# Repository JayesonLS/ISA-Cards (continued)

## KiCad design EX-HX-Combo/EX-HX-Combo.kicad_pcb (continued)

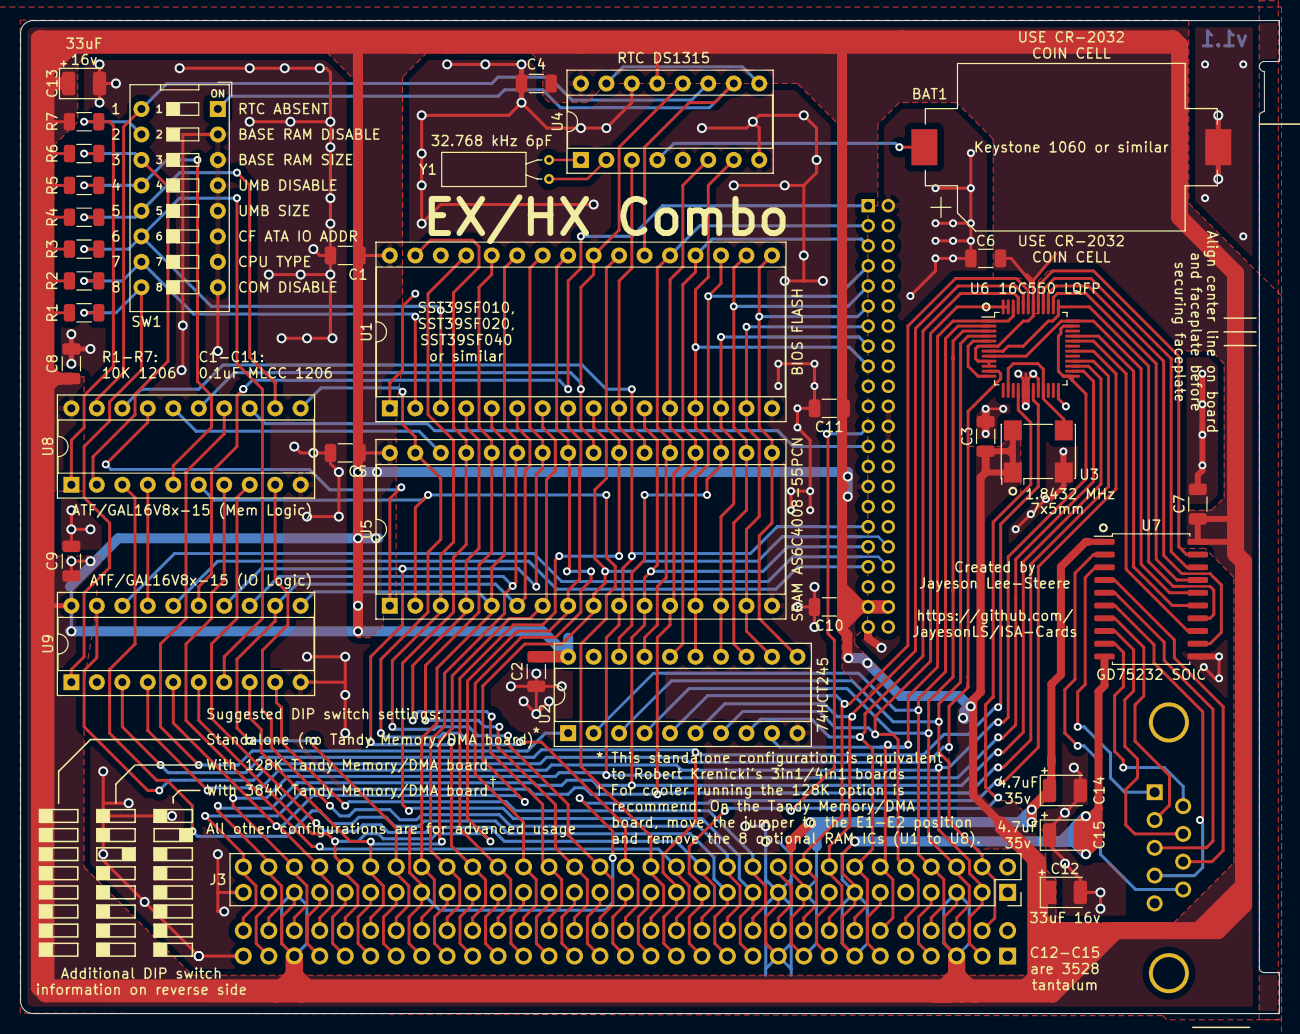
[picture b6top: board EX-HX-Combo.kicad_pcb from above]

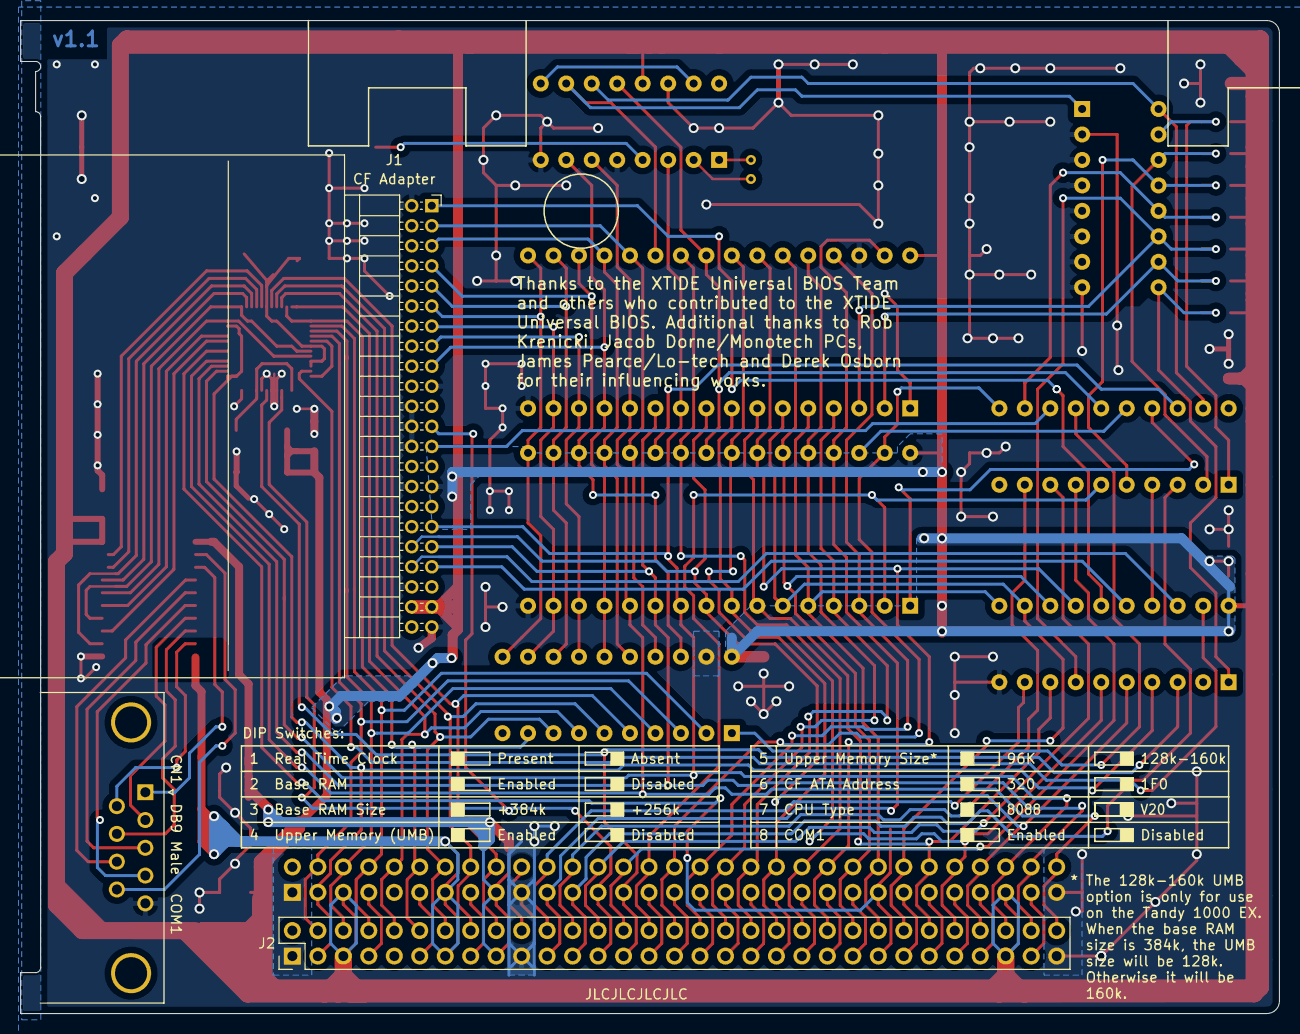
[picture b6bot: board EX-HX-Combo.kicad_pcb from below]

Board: 2 copper layers, 125.5 x 99.0 mm, 38 parts (2 on the bottom side), 107 nets.

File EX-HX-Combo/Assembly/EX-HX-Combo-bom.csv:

Comment,Designator,Footprint,LCSC
"CR2032","BAT1","Battery:BatteryHolder_Keystone_1060_1x2032",""
"0.1uF","C1,C2,C3,C4,C5,C6,C7,C8,C9,C10,C11","Capacitor_SMD:C_1206_3216Metric"," C24497"
"33uF 16v","C12,C13","Capacitor_Tantalum_SMD:CP_EIA-3528-15_AVX-H",""
"4.7uF 35v","C14,C15","Capacitor_Tantalum_SMD:CP_EIA-3528-15_AVX-H",""
"DB9 Male","CN1","w_conn_d-sub:DB_9M",""
"MountingHole_Pad","H1,H2,H3,H4","MountingHole:MountingHole_3.5mm_Pad",""
"AlignmentHole_Pad","H5,H6,H7","00Custom:AlignmentHole",""
"DB-9 Faceplate","H8","00Custom:DB9_Face",""
"IDE_CONNECTOR","J1","Connector_PinSocket_2.00mm:PinSocket_2x22_P2.00mm_Horizontal",""
"Bus_Tandy_Plus","J2","00Custom:TandyPlusSocket",""
"Bus_Tandy_Plus_Through","J3","00Custom:TandyPlusSocket",""
"10K","R1,R2,R3,R4,R5,R6,R7","Resistor_SMD:R_1206_3216Metric","C17902"
"SW_DIP_x10","SW1","Button_Switch_THT:SW_DIP_SPSTx10_Slide_9.78x27.58mm_W7.62mm_P2.54mm",""
"BIOS FLASH","U1","Package_DIP:DIP-32_W15.24mm_Socket","C146583"
"74HCT245","U2","Package_DIP:DIP-20_W7.62mm_Socket","C72118"
"1.8432 MHz","U3","Oscillator:Oscillator_SMD_SeikoEpson_SG8002CA-4Pin_7.0x5.0mm","C386895"
"DS1315","U4","Package_DIP:DIP-16_W7.62mm_Socket","C72115"
"AS6C4008-55PCN","U5","Package_DIP:DIP-32_W15.24mm_Socket","C146583"
"16C550","U6","Package_QFP:LQFP-48_7x7mm_P0.5mm","C181382"
"GD75232N","U7","Package_SO:SOIC-20W_7.5x12.8mm_P1.27mm","C1499602"
"GAL16V8","U8,U9","Package_DIP:DIP-20_W7.62mm_Socket","C72118"
"32.768 kHz","Y1","Crystal:Crystal_C38-LF_D3.0mm_L8.0mm_Horizontal","C182062"

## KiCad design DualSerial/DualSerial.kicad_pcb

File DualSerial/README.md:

Dual Serial
============

*** IN PROGRESS ***

A simple ISA card adding two serial (COM) ports to a vintage PC. 
Created with early Tandy 1000's in mind which have no COM ports from the factory.

Configuration
-------------

Before installing, configure the port selection jumpers to COM ports not yet present 
in the system. Details are located on the board by the port jumpers.

Configure the IRQ jumpers to an approriate selection. For no IRQ, remove the IRQ jumper.
Suggested IRQ settings are located on the board by the IRQ jumpers.

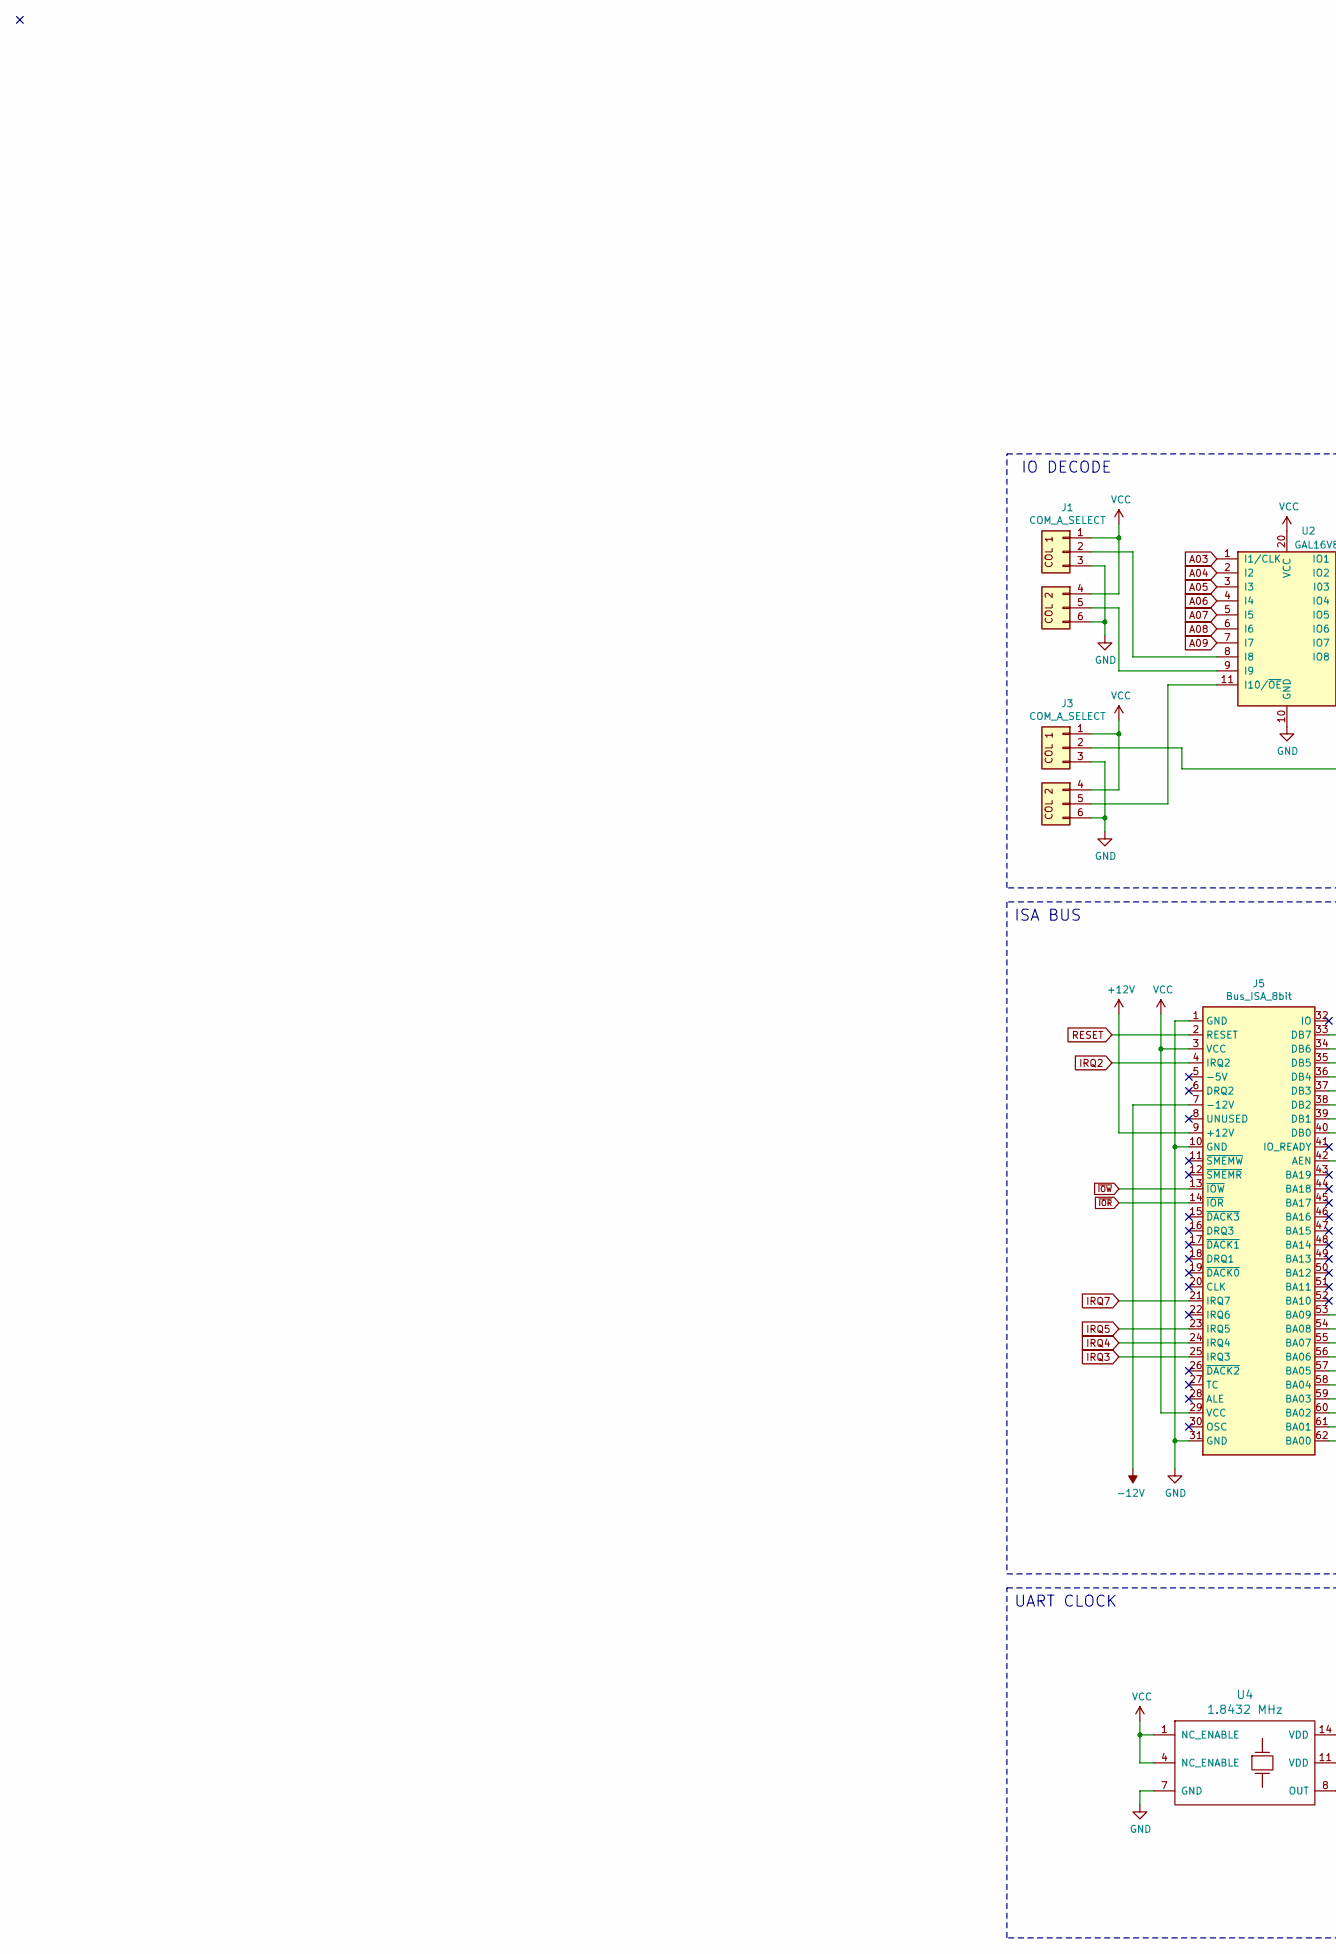
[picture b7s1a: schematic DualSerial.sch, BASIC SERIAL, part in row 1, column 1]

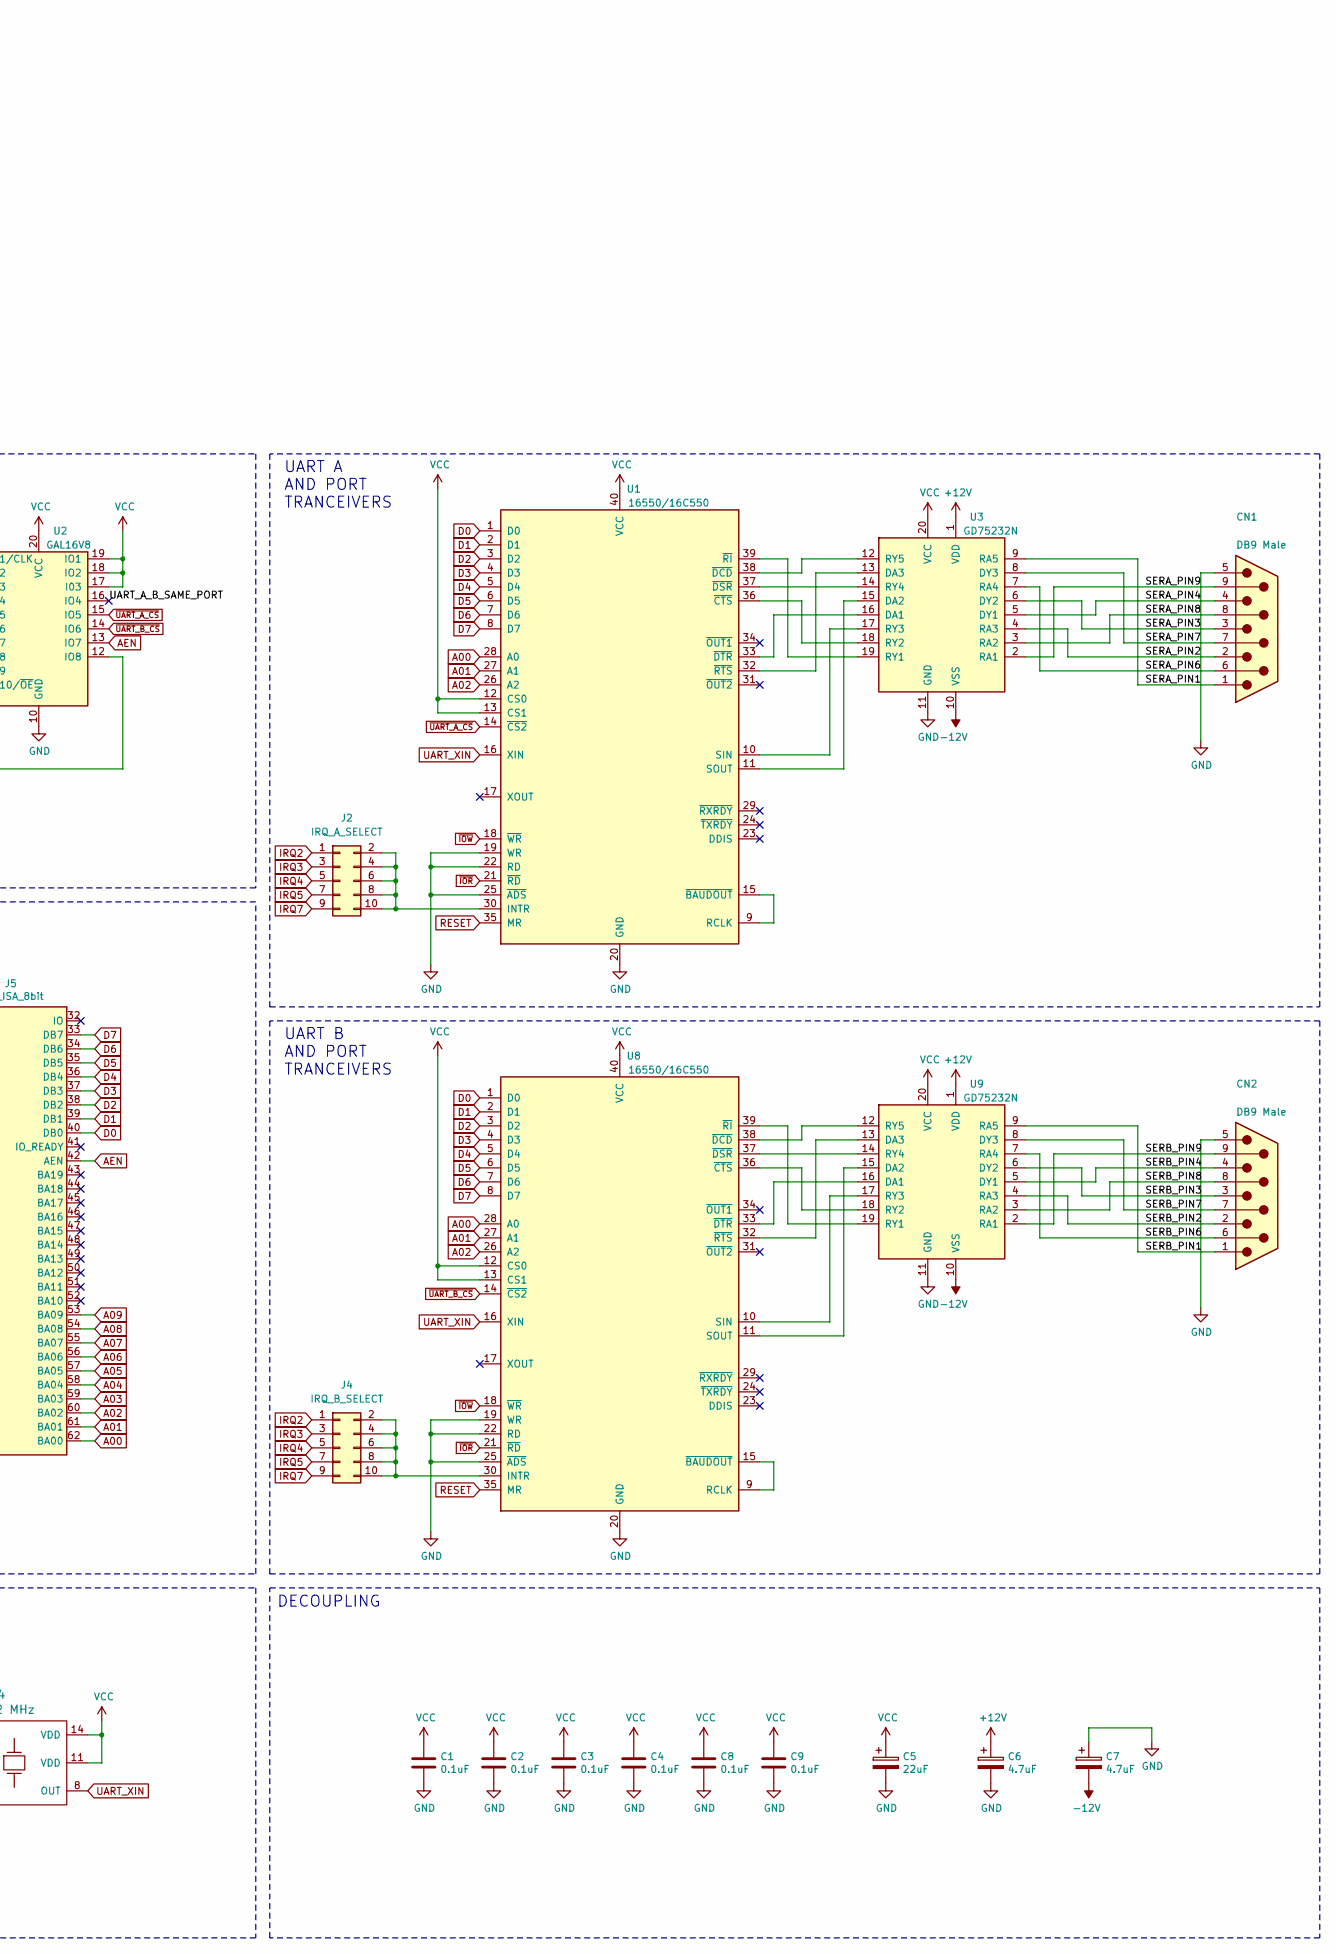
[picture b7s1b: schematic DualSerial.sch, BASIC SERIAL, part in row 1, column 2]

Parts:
C1, C2, C3, C4, C8, C9: 0.1uF; C_Disc_D5.1mm_W3.2mm_P5.00mm
C5: 22uF; CP_Radial_D7.5mm_P2.50mm
C6, C7: 4.7uF; CP_Radial_D7.5mm_P2.50mm
CN1, CN2: DB9 Male; DB_9M
J1, J3: COM_A_SELECT; PinHeader_3x02_P2.54mm_Vertical
J2: IRQ_A_SELECT; PinHeader_2x05_P2.54mm_Vertical
J4: IRQ_B_SELECT; PinHeader_2x05_P2.54mm_Vertical
J5: Bus_ISA_8bit; BUS_XT
U1, U8: 16550/16C550; DIP-40_W15.24mm_Socket
U2: GAL16V8; DIP-20_W7.62mm_Socket
U3, U9: GD75232N; DIP-20_W7.62mm_Socket
U4: 1.8432 MHz; Crystal_DIP8_DIP14

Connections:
+12V: C6.1, J5.9 (+12V), U3.1 (VDD), U9.1 (VDD)
-12V: C7.2, J5.7 (-12V), U3.10 (VSS), U9.10 (VSS)
/SERA_PIN1: CN1.1, U3.9 (RA5)
/SERA_PIN2: CN1.2, U3.4 (RA3)
/SERA_PIN3: CN1.3, U3.6 (DY2)
/SERA_PIN4: CN1.4, U3.5 (DY1)
/SERA_PIN6: CN1.6, U3.7 (RA4)
/SERA_PIN7: CN1.7, U3.8 (DY3)
/SERA_PIN8: CN1.8, U3.3 (RA2)
/SERA_PIN9: CN1.9, U3.2 (RA1)
/SERB_PIN1: CN2.1, U9.9 (RA5)
/SERB_PIN2: CN2.2, U9.4 (RA3)
/SERB_PIN3: CN2.3, U9.6 (DY2)
/SERB_PIN4: CN2.4, U9.5 (DY1)
/SERB_PIN6: CN2.6, U9.7 (RA4)
/SERB_PIN7: CN2.7, U9.8 (DY3)
/SERB_PIN8: CN2.8, U9.3 (RA2)
/SERB_PIN9: CN2.9, U9.2 (RA1)
/UART_A_B_SAME_PORT: U2.16 (IO4)
A00: J5.62 (BA00), U1.28 (A0), U8.28 (A0)
A01: J5.61 (BA01), U1.27 (A1), U8.27 (A1)
A02: J5.60 (BA02), U1.26 (A2), U8.26 (A2)
A03: J5.59 (BA03), U2.1 (I1/CLK)
A04: J5.58 (BA04), U2.2 (I2)
A05: J5.57 (BA05), U2.3 (I3)
A06: J5.56 (BA06), U2.4 (I4)
A07: J5.55 (BA07), U2.5 (I5)
A08: J5.54 (BA08), U2.6 (I6)
A09: J5.53 (BA09), U2.7 (I7)
AEN: J5.42 (AEN), U2.13 (IO7)
D0: J5.40 (DB0), U1.1 (D0), U8.1 (D0)
D1: J5.39 (DB1), U1.2 (D1), U8.2 (D1)
D2: J5.38 (DB2), U1.3 (D2), U8.3 (D2)
D3: J5.37 (DB3), U1.4 (D3), U8.4 (D3)
D4: J5.36 (DB4), U1.5 (D4), U8.5 (D4)
D5: J5.35 (DB5), U1.6 (D5), U8.6 (D5)
D6: J5.34 (DB6), U1.7 (D6), U8.7 (D6)
D7: J5.33 (DB7), U1.8 (D7), U8.8 (D7)
GND: C1.2, C2.2, C3.2, C4.2, C5.2, C6.2, C7.1, C8.2, C9.2, CN1.5, CN2.5, J1.3 (Pin_4), J1.6, J3.3 (Pin_4), J3.6, J5.1 (GND), J5.10 (GND), J5.31 (GND), U1.19 (WR), U1.20 (GND), U1.22 (RD), U1.25 (~ADS~), U2.10 (GND), U3.11 (GND), U4.7 (GND), U8.19 (WR), U8.20 (GND), U8.22 (RD), U8.25 (~ADS~), U9.11 (GND)
IRQ2: J2.1, J4.1, J5.4 (IRQ2)
IRQ3: J2.3, J4.3, J5.25 (IRQ3)
IRQ4: J2.5, J4.5, J5.24 (IRQ4)
IRQ5: J2.7, J4.7, J5.23 (IRQ5)
IRQ7: J2.9, J4.9, J5.21 (IRQ7)
unnamed: J1.2, U2.8 (I8)
unnamed: J1.5, U2.9 (I9)
unnamed: J2.2, J2.4, J2.6, J2.8, J2.10, U1.30 (INTR)
unnamed: J3.2, U2.12 (IO8)
unnamed: J3.5, U2.11 (I10/~OE~)
unnamed: J4.2, J4.4, J4.6, J4.8, J4.10, U8.30 (INTR)
unnamed: U1.10 (SIN), U3.17 (RY3)
unnamed: U1.11 (SOUT), U3.15 (DA2)
unnamed: U1.9 (RCLK), U1.15 (~BAUDOUT~)
unnamed: U1.32 (~RTS~), U3.13 (DA3)
unnamed: U1.33 (~DTR~), U3.16 (DA1)
unnamed: U1.36 (~CTS~), U3.18 (RY2)
unnamed: U1.37 (~DSR~), U3.14 (RY4)
unnamed: U1.38 (~DCD~), U3.12 (RY5)
unnamed: U1.39 (~RI~), U3.19 (RY1)
unnamed: U8.10 (SIN), U9.17 (RY3)
unnamed: U8.11 (SOUT), U9.15 (DA2)
unnamed: U8.9 (RCLK), U8.15 (~BAUDOUT~)
unnamed: U8.32 (~RTS~), U9.13 (DA3)
unnamed: U8.33 (~DTR~), U9.16 (DA1)
unnamed: U8.36 (~CTS~), U9.18 (RY2)
unnamed: U8.37 (~DSR~), U9.14 (RY4)
unnamed: U8.38 (~DCD~), U9.12 (RY5)
unnamed: U8.39 (~RI~), U9.19 (RY1)
RESET: J5.2 (RESET), U1.35 (MR), U8.35 (MR)
UART_XIN: U1.16 (XIN), U4.8 (OUT), U8.16 (XIN)
VCC: C1.1, C2.1, C3.1, C4.1, C5.1, C8.1, C9.1, J1.1, J1.4, J3.1, J3.4, J5.3 (VCC), J5.29 (VCC), U1.12 (CS0), U1.13 (CS1), U1.40 (VCC), U2.17 (I03), U2.18 (IO2), U2.19 (IO1), U2.20 (VCC), U3.20 (VCC), U4.1 (NC_ENABLE), U4.4 (NC_ENABLE), U4.11 (VDD), U4.14 (VDD), U8.12 (CS0), U8.13 (CS1), U8.40 (VCC), U9.20 (VCC)
~IOR: J5.14 (~IOR), U1.21 (~RD~), U8.21 (~RD~)
~IOW: J5.13 (~IOW), U1.18 (~WR~), U8.18 (~WR~)
~UART_A_CS: U1.14 (~CS2~), U2.15 (IO5)
~UART_B_CS: U2.14 (IO6), U8.14 (~CS2~)

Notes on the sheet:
ISA BUS
IO DECODE
UART A AND PORT TRANCEIVERS
UART CLOCK
DECOUPLING
UART B AND PORT TRANCEIVERS

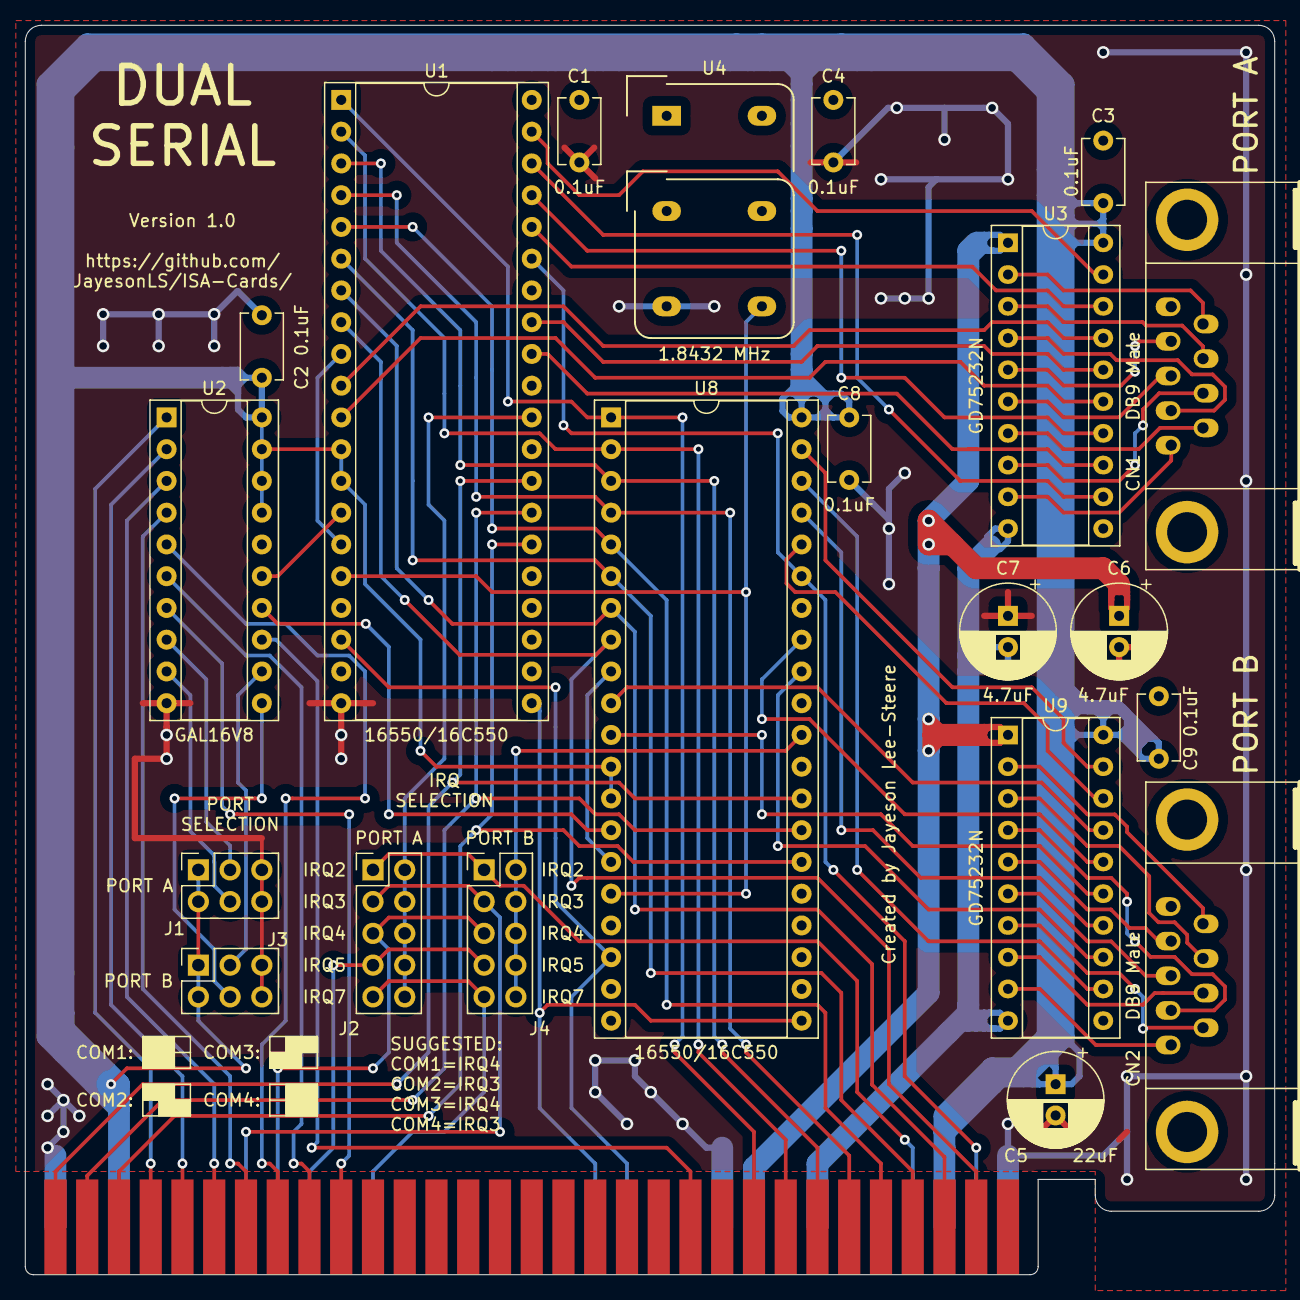
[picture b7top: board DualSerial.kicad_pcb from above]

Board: 2 copper layers, 99.9 x 99.9 mm, 22 parts (0 on the bottom side), 74 nets.

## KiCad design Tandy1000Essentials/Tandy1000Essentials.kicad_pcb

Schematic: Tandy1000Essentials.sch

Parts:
BAT1: CR2032; BatteryHolder_Keystone_103_1x20mm
C1, C2, C3, C4, C5, C6: 0.1uF; C_Disc_D6.0mm_W2.5mm_P5.00mm; Part options C84772,C263183; LCSC C84772
C7: 22uF; CP_Radial_D5.0mm_P2.50mm
H1, H2, H3, H4: MountingHole_Pad; MountingHole_3.5mm_Pad
J1: IDE_CONNECTOR; PinSocket_2x20_P2.54mm_Vertical
J2: CF Adapter Power; PinSocket_1x02_P2.54mm_Vertical
J3: Bus_ISA_8bit; BUS_XT
J4, J5: Addresses; PinHeader_2x03_P2.54mm_Vertical
U1: BIOS FLASH; DIP-32_W15.24mm_Socket
U2: 74HCT245; DIP-20_W7.62mm_Socket
U3: ATF/GAL22V10x-15; DIP-24_W7.62mm_Socket
U4: DS1315; DIP-16_W7.62mm_Socket
U5: AS6C4008-55PCN; DIP-32_W15.24mm_Socket
Y1: 32.768 KHz; Crystal_C38-LF_D3.0mm_L8.0mm_Horizontal

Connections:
/XTAL1: U4.1 (X1), Y1.1
/XTAL2: U4.2 (X2), Y1.2
A00: J3.62 (BA00), U1.12 (A0), U4.6 (D), U5.12 (A0)
A01: J1.35 (A0), J3.61 (BA01), U1.11 (A1), U5.11 (A1)
A02: J1.33 (A1), J3.60 (BA02), U1.10 (A2), U4.3 (~WE), U5.10 (A2)
A03: J1.36 (A2), J3.59 (BA03), U1.9 (A3), U5.9 (A3)
A04: J3.58 (BA04), U1.8 (A4), U3.1 (I1/CLK), U5.8 (A4)
A05: J3.57 (BA05), U1.7 (A5), U3.2 (I2), U5.7 (A5)
A06: J3.56 (BA06), U1.6 (A6), U3.3 (I3), U5.6 (A6)
A07: J3.55 (BA07), U1.5 (A7), U3.4 (I4), U5.5 (A7)
A08: J3.54 (BA08), U1.27 (A8), U3.5 (I5), U5.27 (A8)
A09: J3.53 (BA09), U1.26 (A9), U3.6 (I6), U5.26 (A9)
A10: J3.52 (BA10), U1.23 (A10), U5.23 (A10)
A11: J3.51 (BA11), U1.25 (A11), U5.25 (A11)
A12: J3.50 (BA12), U1.4 (A12), U5.4 (A12)
A13: J3.49 (BA13), U1.28 (A13), U5.28 (A13)
A14: J3.48 (BA14), U1.29 (A14), U5.3 (A14)
A15: J3.47 (BA15), U3.8 (I8), U5.31 (A15)
A16: J3.46 (BA16), U3.9 (I9), U5.2 (A16)
A17: J3.45 (BA17), U3.10 (I10), U5.30 (A17)
A18: J3.44 (BA18), U3.11 (I11), U5.1 (A18)
ATA_ADDR_JUMPER: J4.4, U1.3 (A15), U3.22 (IO2)
D0: J3.40 (DB0), U2.2 (A0)
D0_BUF: J1.17 (D0), U1.13 (D0), U2.18 (B0), U4.7 (Q), U5.13 (DQ0)
D1: J3.39 (DB1), U2.3 (A1)
D1_BUF: J1.15 (D1), U1.14 (D1), U2.17 (B1), U5.14 (DQ1)
D2: J3.38 (DB2), U2.4 (A2)
D2_BUF: J1.13 (D2), U1.15 (D2), U2.16 (B2), U5.15 (DQ2)
D3: J3.37 (DB3), U2.5 (A3)
D3_BUF: J1.11 (D3), U1.17 (D3), U2.15 (B3), U5.17 (DQ3)
D4: J3.36 (DB4), U2.6 (A4)
D4_BUF: J1.9 (D4), U1.18 (D4), U2.14 (B4), U5.18 (DQ4)
D5: J3.35 (DB5), U2.7 (A5)
D5_BUF: J1.7 (D5), U1.19 (D5), U2.13 (B5), U5.19 (DQ5)
D6: J3.34 (DB6), U2.8 (A6)
D6_BUF: J1.5 (D6), U1.20 (D6), U2.12 (B6), U5.20 (DQ6)
D7: J3.33 (DB7), U2.9 (A7)
D7_BUF: J1.3 (D7), U1.21 (D7), U2.11 (B7), U5.21 (DQ7)
unnamed: BAT1.1 (+), U4.4 (BAT1)
unnamed: U4.9 (ROM/~RAM), U4.15 (Vcc0)
RESET: J3.2 (RESET), U3.7 (I7)
ROM_ADDR_JUMPER: J4.3, U3.23 (IO1)
V20_JUMPER: J5.3, U1.2 (A16)
VCC: C1.1, C2.1, C3.1, C4.1, C5.1, C6.1, C7.1, J1.29 (~DACK), J1.38 (~CS3), J2.1, J3.3 (VCC), J3.29 (VCC), J4.1, J4.2, J5.1, U1.32 (VCC), U2.20 (VCC), U3.24 (VCC), U4.13 (~RST), U4.16 (Vcc1), U5.32 (VCC)
~CE~_BIOS: J5.4, U1.22 (CE)
~CE~_BIOS_DECODE: J5.2, U3.18 (IO6), U4.11 (~CEI)
~CE~_BIOS_THRU: J5.6, U4.10 (~CEO)
~CS1~_ATA: J1.37 (~CS1), U3.19 (IO5)
~IOR: J3.14 (~IOR), U3.21 (I03)
~IOR_OR_MEMR: U2.1 (A->B), U3.15 (IO9)
~IOR~_DELAYED: J1.25 (~IOR), U3.14 (IO10)
~IOW: J1.23 (~IOW), J3.13 (~IOW)
~MEMR: J3.12 (~SMEMR), U3.17 (IO7)
~MEMR~_DELAYED: U1.24 (OE), U3.16 (IO8), U4.12 (~OE), U5.24 (OE#)
~MEMW: J3.11 (~SMEMW), U1.31 (PGM), U5.29 (WE#)
~RESET: J1.1 (~RESET), U3.20 (IO4)

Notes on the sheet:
ISA BUS
DECOUPLING
DATA BUFFERING
DECODING
BIOS
CF ADAPTER
JUMPERS
REAL TIME CLOCK (OPTIONAL)
512K SRAM

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
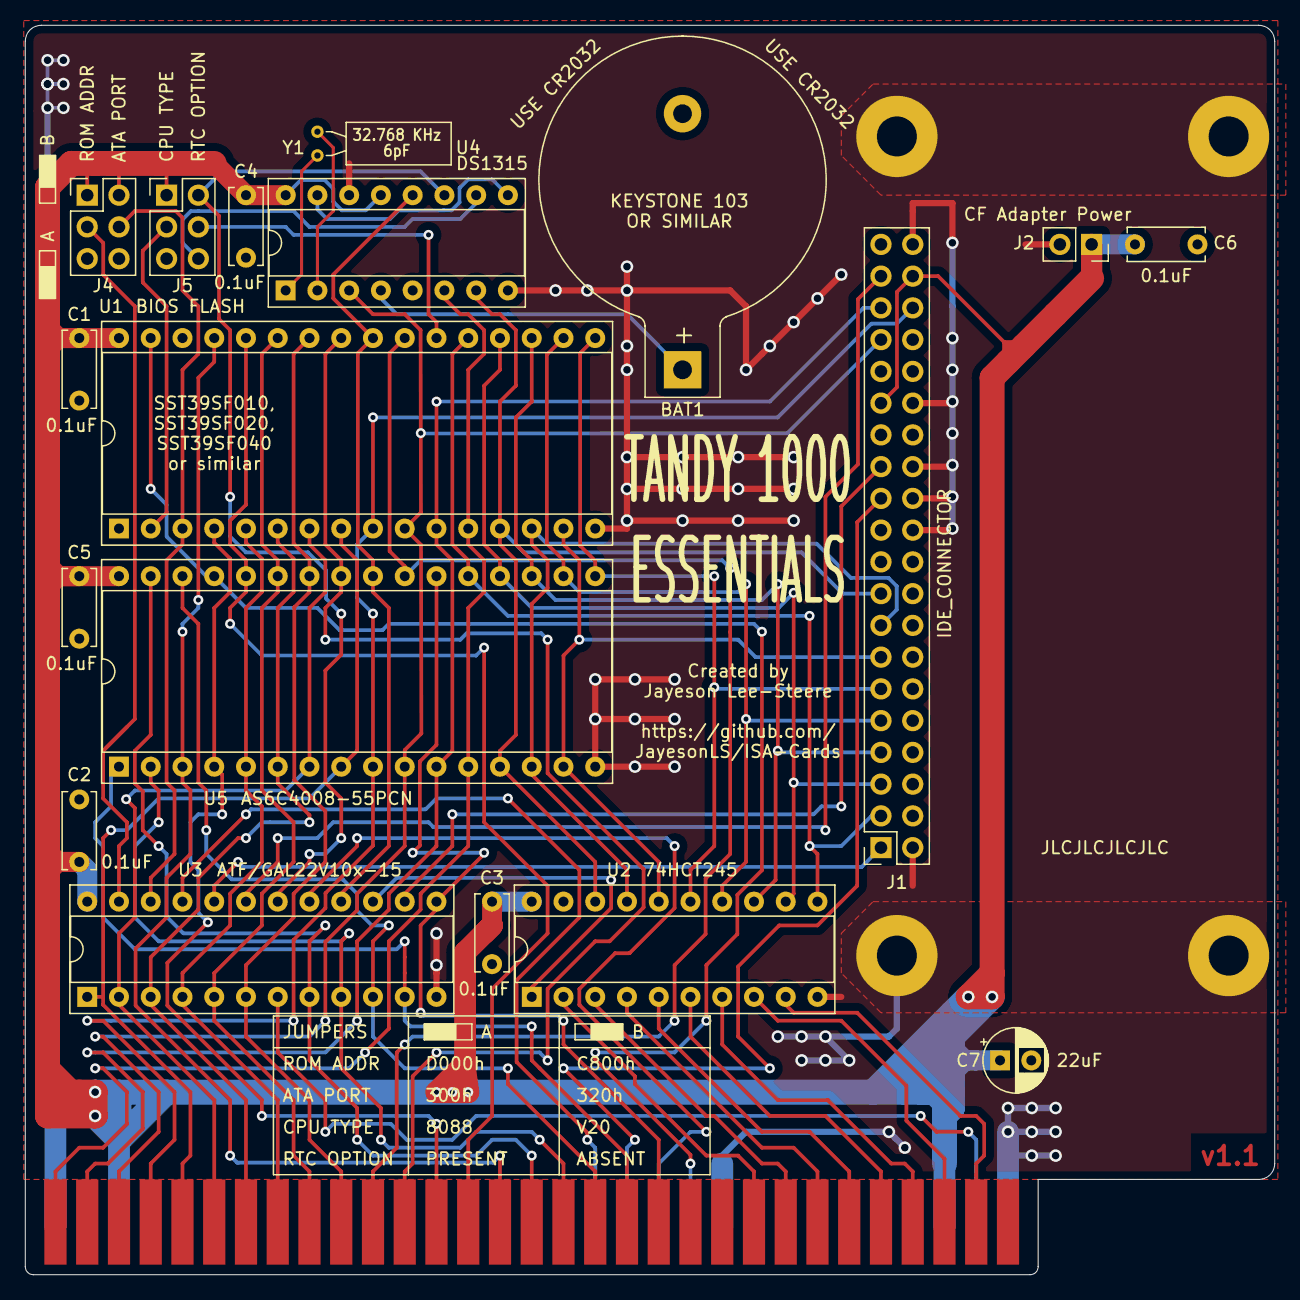
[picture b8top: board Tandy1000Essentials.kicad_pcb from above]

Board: 2 copper layers, 99.9 x 99.9 mm, 23 parts (0 on the bottom side), 58 nets.

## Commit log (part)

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2021-02-27 Add root LICENSE file.
2021-02-27 Add Libraries.
2021-02-27 Add Template board design.
2021-02-28 Add IDE/ATA connector to Template.
2021-02-28 Add global labels to the ISA bus connector,
2021-02-28 Add IC's to schematic and PCB.
2021-02-28 CF-Super-Lite: Label most IC pins and IDE connector.
2021-02-28 CF-Super-Lite: Added a bunch of premature layout.
2021-03-01 More premature layout work.
2021-03-02 Add power for CF adapter to Template and CF-Super-Lite.
2021-03-02 Finish remaining IDE signal directions based on the ATA spec rev 1. Correct IDE address assignments and route the new connections on the PCB.
2021-03-02 Removed /CS3 output from GAL as XT-IDE doesn't seem to use it. Wemoved A14 to GAL meaning BIOS now has a 32k range in memory rather than 16k. Used freed pins to implement RESET inversion.
2021-03-05 CF-Super-Lite: Final board tweaks before sending to production.
2021-03-05 CF-Super-Lite gerbers.
2021-03-13 CF-Super-Lite: Swap dip switch and resistor array for jumper block.
2021-03-13 Add missing 3x3 pin header footprint.
2021-03-13 First pass on CF-Clock-Combo.
2021-03-13 CF-Clock-Combo: Tidy up schematic.
2021-03-13 CF-Clock-Combo: Minor silkscreen changes.
2021-03-13 Initial work on Tandy 1000 essentials board.
2021-03-14 Tandy1000Essentials: More refinement of layout, fix ERC error due to incorrect 22V10 pinout.
2021-04-01 Tandy 1000 Essentials: Finish pass at tidying layout.
2021-04-18 First pass at schematic for Basic Serial card.
2021-04-18 BasicSerial: Fix ERC issues, include AEN in IO addr decode, assign footprints.
2021-04-18 Add backplane outline to Template.
2021-04-18 BasicSerial: Place DB-9 connector.
2021-04-18 BasicSerial: Initial layout work.
2021-04-20 BasicSerial: Reduce size of board so it is only as tall as needed by the serial connector.
2021-04-21 Basic Serial: Add +-12v decoupling caps. WIP on board routing.
2021-04-22 BasicSerial: Reduce 0.34mm track widths to 0.3mm. Minor sikscreen changes.
2021-04-22 BasicSerial: Plot schematic.
2021-04-22 Add gerbers
2021-04-23 BasicSerial: Change filename of GAL logic
2021-04-23 Add initial work on DualSerial project. Based on BasicSerial.
2021-04-23 Finish DualSerial decode logic.
2021-04-23 Fix BasicSerial decode logic - was accidentally reading in unused pin.
2021-04-23 DualSerial: Add debug output signal for whether A and B port are configured the same.
2021-04-24 DualSerial: WIP on PCB layout.
2021-04-25 DualSerial: Mostly finished first pass of PCB layout. Still needs component values added and A/B ports are in opposite of desired order.
2021-04-25 DualSerial: Add component labels to board.
2021-04-25 Dual Serial: Minor silk screen change.
2021-04-25 DualSerial: Change to ground plan vias in top left corner.
2021-04-25 DualSerial: Update GAL decode logic to match modified pinout.
2021-04-25 DualSerial: Minor layout changes.
2021-04-25 DualSerial: Reduce size of PCB tab added in the previous commit.
2021-04-29 Initial work on ISA riser board.
2021-04-29 Initial pass at ISAtoTandyPlus
2021-04-30 Continuing work on ISA riser card.
2021-05-01 Finished first pass on riser card.
2021-05-03 Fix location of CF adapter power for all boards that use it. Also the mounting holes in the schematic for the same boards. Finishing touches to Tandy 1000 Essentials.
2021-05-06 Gerbers for multiple boards. Minor tweaks to some boards.
2021-06-12 Tandy1000Essentials: Fixes to PCB and temporary changes to programmable logic for testing. Will need to determine best choice for BIOS addresses and ports.
2021-06-12 Remove CF-Super-Lite and CF-Clock-Combo. Will instead focus only the SRAM/Clock/CF combo which can be configured into the simpler versions.
2021-06-12 CF-Combo-Super-Lite: Note that SmartWatch and clock are optional.
2021-06-12 Template: Fix orientation of CF adapter header (rotate 180 degrees).
2021-06-12 CF-Super-Lite-Combo: Rotate CF adapter header 180 degrees. Routing still needs to be corrected.
2021-06-13 CF-Super-Lite-Combo: Finished pass at fixing layout. Ready for production.
2021-06-13 Rename CF-Super-Lite-Combo back to CF-Combo.
2021-06-13 Add gerbers for CF-Combo-Super-Lite.
2021-06-19 Initial work on EX-HX Combo. Just a first pass at the schematic.
2021-06-19 And Tandy Plus bus to shared library.
2021-06-19 EX-HX-Combo: Add schematic PDF
2021-06-19 EX-HX-Combo: Add a pass at the memory decode logic.
2021-06-20 Rename Template to IsaTemplate
2021-06-20 Start on Tandy Plus template.
2021-06-20 Work on Tandy Plus template.
2021-06-20 Add COM IRQ selection to EX-HX-Combo.
2021-06-20 Additional work on Tandy Plus template.
2021-06-24 Complete first pass at Tandy Plus template by adding bracket details.
2021-06-24 Mods to EX-HX-Combo.
2021-06-24 Remove incorrect internal edge cut circules from Tandy Plus Template.
2021-06-24 Mods to initial PCB sizing for EX-HX combo.
2021-06-24 Add mounting holes to EX-HX-Combo schematic.
2021-06-24 WIP on EX-HX-Combo.
2021-06-25 EX-HX-Combo: Properly add pass-through into schematic.
2021-06-25 Update EX-HX schematic PDF.
2021-06-26 EX-HX-Combo layout WIP.
2021-06-27 EX-HX-Combo WIP. Serial section coming along.
2021-06-27 EX-HX-Combo: Switch to scheme with bottom layer horizontal, top layer vertical since that matches the existing serial section better.
2021-07-11 Add ROM binaries for CF-Combo-Super-Lite.
2021-07-31 Add missing cache file update.
2021-07-31 Add image of CF-Combo-Super-Lite
2021-08-11 More WIP on redo of through hole layout for EX-HX Combo.
2021-08-12 More layout work on EX-HX combo.
2021-08-13 EX-HX-Combo layout work: All connections have been made, in progress on tidy up.
2021-08-13 Add alignment tabs to EX-HX-Combo.
2021-08-13 EX-HX-Combo layout work.
2021-08-13 More EX-HX Combo layout work.
2021-08-14 EX-HX-Combo: A little bit of power work for the CF connector.
2021-08-14 Reorder dip switches on EX-HX-Combo.
2021-08-15 Lots of layout cleanup on EX-HX-Combo.
2021-08-15 First pass of track layout complete on EX-HX-Combo. Still need to polish power full and vias.
2021-08-16 EX-HX-Combo power fill and via first pass completed.
2021-08-16 EX-HX-Combo: Checked that crystal oscillator footprint is fine. Minor silkscreen changes.
2021-08-16 EX-HX-Combo: Prepare for moving faceplate.
2021-08-16 EX-HX-Combo: Relocated the faceplate into final position.
2021-08-16 EX-HX-Combo: Connect faceplace to board. Pass on board complete.
2021-08-16 EX-HX-Combo: Updated GAL logic to match current pinouts. Needed to reorder some pins on MemLogic due to logic compile errors.
2021-08-16 EX-HX-Combo: Commit gerbers.
2021-08-18 EX-HX-Combo: Move backplate back to original position in prep for moving to new scene.
2021-08-18 WIP on EX-HX-Combo backplate.
2021-08-18 EX-HX-Combo: Single backplate for testing.
2021-08-19 Alternative EX-HX-Combo-Backpate designed for Aluminium manufacture.
2021-08-26 CF-Combo-Super-Lite: Add additional bypass cap to CF power. Add back in V20+ jumper (selects different flash ROM range). Add version number. Initial work setting up for JLCPCB production, however the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
2021-08-26 EX-HX-Combo: Initial work preparing for JLCPCB assembly. Other minor tweaks also.
2021-08-27 EX-HX-Combo: More work preparing for JLCPCB assembly.
2021-09-11 Add BIOS files to XTA-interface. Still need to locate an actual WD BIOS - just all zeros for the moment.
2021-09-11 Add XTA connector symbol.
2021-09-11 WIP on XTA interface card.
2021-09-12 More WIP on XTA interface card.
2021-09-13 WIP on XTA interface layout.
2021-09-13 Finish first pass of layout of XTA interface card.
2021-09-13 Finished first pass on board design.
2021-09-13 Minor XTA interface tweaks.
2021-09-14 Add left GAL logic for XTA interface. Involved one pin swap to account for two of the 16V8 pins not having feedback.
2021-09-14 Add right GAL logic for XTA interface. Resulted in several circuit/board changes.
2021-09-14 Swap positions of A and B jumpers.
2021-09-15 Use correct DB-9 footprint on EX-HX-Combo. Also remove ground from alighment pins and space out the resitors in the top left bank.
2021-09-15 EX-HX-Combo: Change jumper block setup. Remove COM port and IRQ options. Now fixed to COM1 and IRQ4. Add a jumper for V20+ processor.
2021-09-26 EX-HX-Combo: Fix a couple of errors in the GAL logic. The GAL logic still needs to be updated to match the current schematic.
2021-09-26 EX-HX-Combo: WIP on backplate refinements.
2021-09-26 EX-HX-Combo: Relocate back plate alignment tabs to very ends of boards. Also make them 1mm narrower. Remove middle alighment tab.
2021-09-26 TandyPlusTemplate: Moved back plate 0.8mm to the right to better match Tandy dimensions. Remove 1mm from the top edge of the 100x100mm board outline as this was not valid for a board in the middle po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
2021-09-26 EX-HX-Combo: Update GAL logic to match current board design.
2021-09-26 Minor EX-HX-Combo refinements.
2021-09-26 EX-HX-Combo. Production files.
2021-09-27 XTA-Interface: Set up ROMs for 32K windowing,
2021-09-28 EX-HX-Combo: Remove area of ground copper pour where CF adapter jumper pins might scratch through solder mask. Rework footprint for dip switches to be easier on production folks. Round corners of boa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
2021-09-28 XTA-Interface: Change tantalum capacitor value text.
2021-10-06 Rename CF-Combo-Super-Lite to Tandy 1000 Essentials. The design is missing use of the AEN signal which makes it only suitable for use in the Tandy 1000 configuration.
2021-10-06 Copy Tandy1000Essentials / CF-Super-Lite to CFSuperCombo. This will become a more capable upgrade board.
2021-10-06 Tandy 1000 Essentials: Remove references to non-Tandy 1000 configurations.
2021-10-06 Copy CF-Combo-Super-Lite to Tandy 1000 Essentials. The design is currently missing use of the AEN signal which makes it only suitable for use in the Tandy 1000 configuration. Plan is to do a simpler 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
2021-10-06 Tandy 1000 Essentials: Remove references to non-Tandy 1000 configurations.
    (cherry picked from commit 135775326dfe376c111a82a9d818a20a770e5fad)
2021-10-06 Rename CF-Combo-Super-Lite to CFSuperLite in preparation for simplifying design while fixing the AEN issue.
2021-10-06 Remove duplicate JLCJLCJLCJLC silscreen text.
2021-10-06 CFSuperLite: Mostly schematic work to direct-connect the SST flash to bus. Remove now-redundant signals from the glue and switch to a smaller 16V8 GAL. Layout needs to be redone. Should change some c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
2021-10-06 Update EX-HX-Combo and XTA-Interface to use updated 16v8 component.
2021-10-06 WIP on CFSuperLite layout. Switched it to use a dip switch rather than jumpers.
2021-10-07 CFSuperLite: DRC passing and all pads connected. Needs clean up.
2021-10-07 CFSuperLite layout cleanup WIP.
2021-10-08 CFSuperLite: Finished first pass on layout.
2021-10-08 CFSuperLite: Complete first pass on silkscreen. Board is complete.
2021-10-08 EX-HX-Combo: Switch clock crystal part. The previously chosen part is actually a SMT part and kind of expensive.
2021-10-09 Add remaining LCSC part numbers to CFSuperLite symbols. Update bom file.
2021-10-09 Copy CFSuperLite to PCSuperCombo in prep for creating that new design.
2021-10-09 Rename CFSuperLite GAL logic files before making functional updates.
2021-10-09 PCSuperCombo: Increase board outline to ~127x107mm.
2021-10-09 Update edge connector footprint on CFSuperLite
2021-10-09 PCSuperCombo: Update edge connector footprint. Extend ground fill to edges.
2021-10-09 PCSuperCombo: Early WIP.
2021-10-09 PCSuperCombo: Early layout work.
2021-10-10 CFSuperLite: Duplicate J1 assembling instructions on rear side.
2021-10-10 PCSuperCombo: Complete glue connectons to GAL's. Add circuit for LED drive.
2021-10-10 PCSuperCombo: Remove CARD_SEL output from GAL logic. We are already generating this signal to set the direction of the '245 on the board.
2021-10-10 Save off the corrected DIP switches to the local library.
2021-10-10 CFSuperLite: Add option to use 3-way DIP switch and 0 ohm resistor for assembly variation without RTC parts.
2021-10-11 Initial work on addiing serial to PCSuperCombo.
2022-06-04 Update license.
